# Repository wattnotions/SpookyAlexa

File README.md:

# SpookyAlexa
Control software for an animatronic mask plugged into an Amazon Alexa

For explanation of this project visit http://www.wattnotions.com/spooky-alexa-mask-documentation/

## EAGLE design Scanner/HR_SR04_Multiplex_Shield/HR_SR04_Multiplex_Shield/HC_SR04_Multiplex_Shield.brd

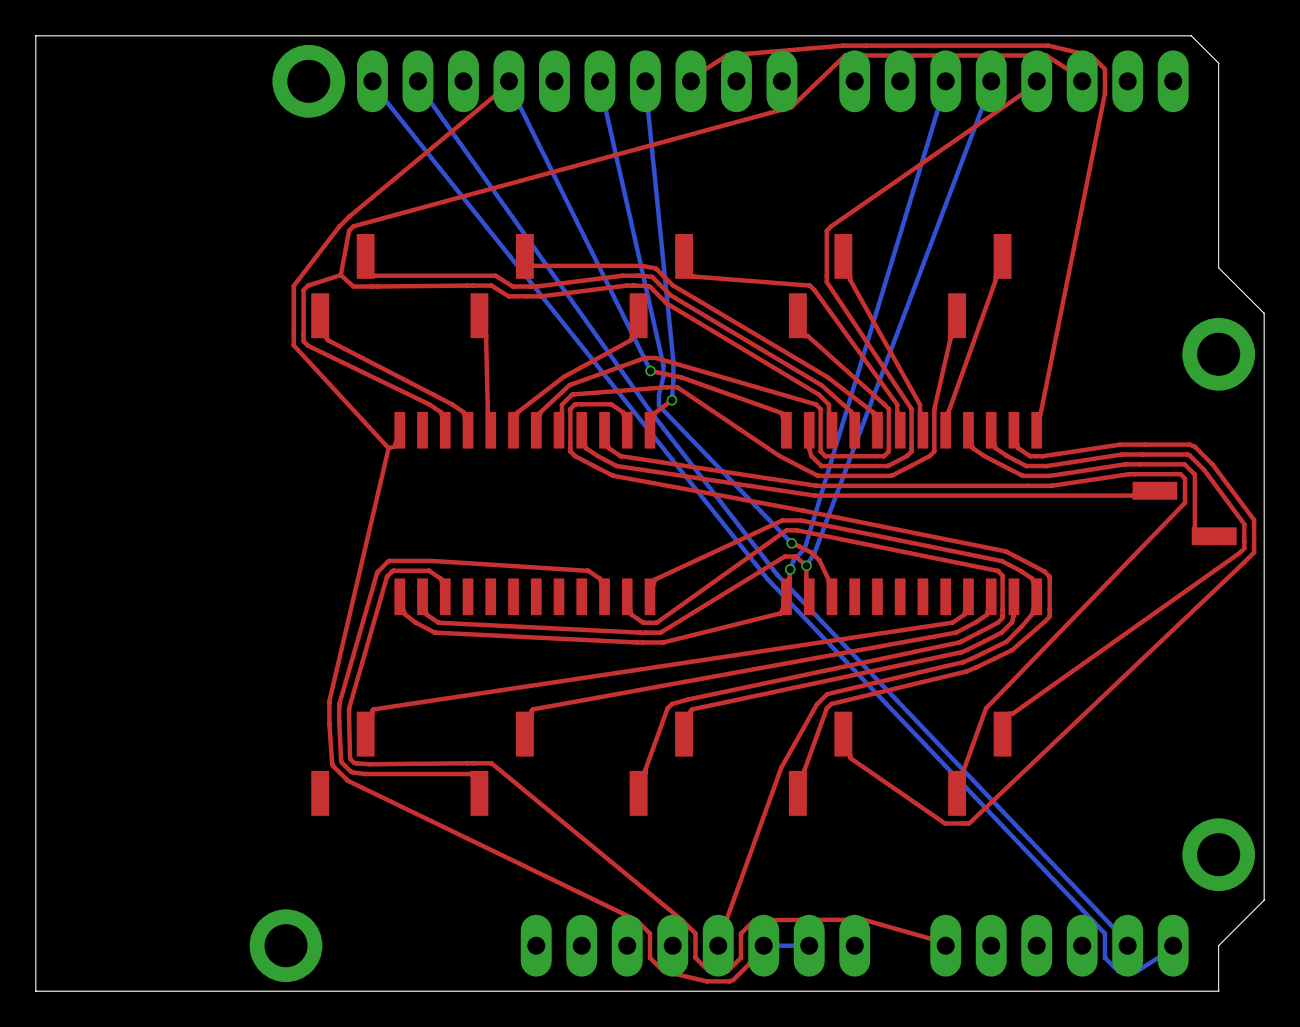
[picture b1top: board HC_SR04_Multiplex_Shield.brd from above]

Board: 2 copper layers, 68.6 x 53.3 mm, 21 parts (0 on the bottom side), 33 nets.

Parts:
J1, J2, J3, J4, J5, J6, J7, J8, J9, J10, J11: Connector_PinHeader_2.54mm:PinHeader_1x02_P2.54mm_Vertical_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
P1, P4: Socket_Arduino_Uno:Socket_Strip_Arduino_1x08
P2: Socket_Arduino_Uno:Socket_Strip_Arduino_1x06
P3: Socket_Arduino_Uno:Socket_Strip_Arduino_1x10
P5, P6, P7, P8: Socket_Arduino_Uno:Arduino_1pin
U1: Package_SO:SOIC-24W_7.5x15.4mm_P1.27mm
U2: Package_SO:SOIC-24W_7.5x15.4mm_P1.27mm::1

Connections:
+5V: P1.5, U1.24, U2.24
/2: P4.6, U1.10, U2.10
/3: P4.5, U1.11, U2.11
/4: P4.4, U1.14, U2.14
/5: P4.3, U1.13, U2.13
/10(ECHO): P3.8, U1.1
/11(TRIG): P3.7, U2.1
/12: P3.6, U1.15
/A0: P2.1, U2.15
/A4(SDA): P2.5, P3.2
/A5(SCL): P2.6, P3.1
/E1: J1.1, U1.9
/E2: J2.1, U1.8
/E3: J3.1, U1.7
/E4: J4.1, U1.6
/E5: J5.1, U1.5
/E6: J6.1, U1.4
/E7: J7.1, U1.3
/E8: J8.1, U1.2
/E9: J9.1, U1.23
/E10: J10.1, U1.22
/E11: J11.1, U1.21
/T1: J1.2, U2.9
/T2: J2.2, U2.8
/T3: J3.2, U2.7
/T4: J4.2, U2.6
/T5: J5.2, U2.5
/T6: J6.2, U2.4
/T7: J7.2, U2.3
/T8: J8.2, U2.2
/T9: J9.2, U2.23
/T10: J10.2, U2.22
GND: P1.6, P1.7, P3.4, U1.12, U2.12

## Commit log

2019-11-16 got gpio toggle working D2-d8, a1-15
2019-11-28 completed schematic of board
2019-11-28 export spectra file for topor import
2019-11-28 flipped components to make usb access easier
2019-11-28 fixed unconnected nets
2019-11-28 exported topor autoroute, still needs some work
2019-12-02 routed and ready for manufacture
2019-12-02 added "SpookyAlexa" silk text
2019-12-02 removed ground plane bcuz it looks cooler
2020-01-11 added working example
2020-01-12 got binary port count working
2020-01-17 got main sensor read loop working
2020-01-17 added printSensorVals function
2020-01-17 added selectSensor function
2020-01-17 added NUM_SENSORS def
2020-01-17 got rough location tracking working
2020-03-10 added datasheet for esp32
2020-03-27 got angle calc in degrees working
2020-03-27 added 180 degree line plots
2020-06-09 stated kicad pcb design
2020-06-09 added arduino nano schematic
2020-06-09 changed dir structure
2020-06-09 changed dir name
2020-06-09 last working version from video
2020-07-04 started schematic
2020-07-05 schematic progressed 20% completed
2020-07-11 started audio section of schematic
2020-07-16 finished analog schematic layout part
2020-07-29 changed op amp to tlv2372
2020-07-31 changed 3.5mm jack to 1503 09 part symbol
2020-08-03 all footprints matched to symbols
2020-08-03 started board layout
2020-08-03 footprints placed, ready for routing
2020-08-09 routing completed
2020-08-09 silkscreen text partially finished
2020-08-10 silk screen done, board finished
2020-09-09 cleaned up dfu pullups on schematic - added buttons
2020-09-09 added vcap caps
2020-09-09 added pwr + indication leds
2020-09-09 ADDED LABS NRST AND USR_SW
2020-09-16 v0.2 routing started
2020-09-17 v0.2 routing completed
2020-09-20 fixed missing envelope out trace
2020-09-20 ran DRC and fixed 2 issues
2020-09-20 cleaned up silk screen
2020-09-20 moved pin 0 ref for microcontroller
2020-09-21 changed c3 to 1206, generated jlcpcb fab files
